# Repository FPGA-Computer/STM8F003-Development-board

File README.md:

This is a quick and dirty STM8F003 development board.

Initial PCB release - first layout/non-tested

PCB/ Eagle CAD files and Sketch3D model

Project page is at 
http://hw-by-design.blogspot.com/2018/07/stm8-breakout-board-with-usb-serial.html

This work is licensed under a 
Attribution 4.0 International (CC BY 4.0)

The full detail of this license is available at: 
https://creativecommons.org/licenses/by/4.0/

I messed up on the CC license version number on the CAD.  Treat it as 4.0.

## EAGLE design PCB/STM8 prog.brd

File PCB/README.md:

This is a quick and dirty STM8F003 development board.

Initial PCB release - first layout/non-tested

PCB/  - Eagle CAD filesand Sketch3D model

Hackaday project page is at 
https://hackaday.io/project/18286-misc-8-bit-uc-projects/log/54286-stm8-breakout-board-with-usb-serial

This work is licensed under a 
Attribution 4.0 International (CC BY 4.0)

The full detail of this license is available at: 
https://creativecommons.org/licenses/by/4.0/

I messed up on the CC license version number on the CAD.  Treat it as 4.0.

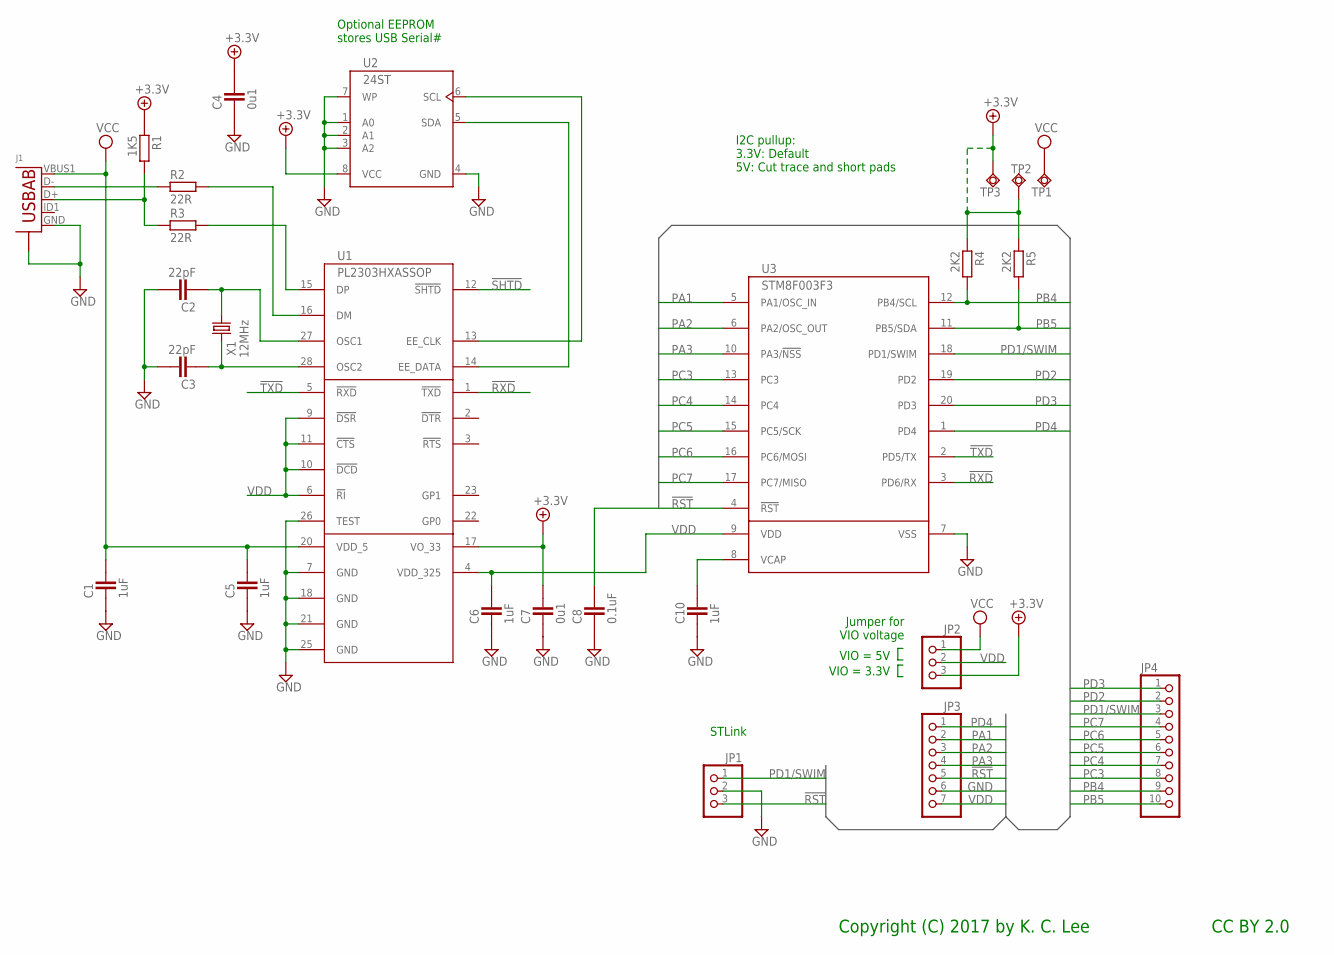
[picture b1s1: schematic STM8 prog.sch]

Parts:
C1, C5, C6, C10: 1uF; CAPC1608X92N
C2, C3: 22pF; CAPC1608X92N
C4, C7: 0u1; CAPC1608X92N
C8: 0.1uF; CAPC1608X92N
J1: USB-ABBG; USB-AB-MICRO-SMD_V03_SF
JP1, JP2: PINHD-1X3; 1X03
JP3: PINHD-1X7_2.54; 1X07
JP4: PINHD-1X10; 1X10
R1: 1K5; RESC1608X55N
R2, R3: 22R; RESC1608X55N
R4, R5: 2K2; RESC1608X55N
TP1, TP2, TP3: TPSQTP09SQ; TP09SQ
U1: PL2303HXASSOP; SSOP28DB
U2: 24ST; TSSOP8
U3: STM8F003F3; TSSOP20
X1: 12MHz; HC49U-V

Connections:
!RST: C8.2, JP1.3, JP3.5, U3.4 (!RST)
!RXD: U1.1 (!TXD), U3.3 (PD6/RX)
!SHTD: U1.12 (!SHTD)
!TXD: U1.5 (!RXD), U3.2 (PD5/TX)
+3.3V: C4.2, C7.2, JP2.3, R1.1, R4.1, R5.1, TP2.TP, TP3.TP, U1.17 (VO_33), U2.8 (VCC)
GND: C1.1, C2.2, C3.2, C4.1, C5.1, C6.1, C7.1, C8.1, C10.1, J1.GND, J1.S1 (S), J1.S2 (S), J1.S3 (S), J1.S4 (S), JP1.2, JP3.6, U1.7 (GND), U1.18 (GND), U1.21 (GND), U1.25 (GND), U1.26 (TEST), U2.1 (A0), U2.2 (A1), U2.3 (A2), U2.4 (GND), U2.7 (WP), U3.7 (VSS)
unnamed: C10.2, U3.8 (VCAP)
unnamed: R3.2, U1.15 (DP)
unnamed: J1.D+, R1.2, R3.1
unnamed: J1.D-, R2.1
unnamed: R2.2, U1.16 (DM)
unnamed: U1.14 (EE_DATA), U2.5 (SDA)
unnamed: U1.13 (EE_CLK), U2.6 (SCL)
unnamed: C2.1, U1.27 (OSC1), X1.1
unnamed: C3.1, U1.28 (OSC2), X1.2
PA1: JP3.2, U3.5 (PA1/OSC_IN)
PA2: JP3.3, U3.6 (PA2/OSC_OUT)
PA3: JP3.4, U3.10 (PA3/!NSS)
PB4: JP4.9, R4.2, U3.12 (PB4/SCL)
PB5: JP4.10, R5.2, U3.11 (PB5/SDA)
PC3: JP4.8, U3.13 (PC3)
PC4: JP4.7, U3.14 (PC4)
PC5: JP4.6, U3.15 (PC5/SCK)
PC6: JP4.5, U3.16 (PC6/MOSI)
PC7: JP4.4, U3.17 (PC7/MISO)
PD1/SWIM: JP1.1, JP4.3, U3.18 (PD1/SWIM)
PD2: JP4.2, U3.19 (PD2)
PD3: JP4.1, U3.20 (PD3)
PD4: JP3.1, U3.1 (PD4)
VCC: C1.2, C5.2, J1.VBUS1 (VBUS), JP2.1, TP1.TP, U1.20 (VDD_5)
VDD: C6.2, JP2.2, JP3.7, U1.4 (VDD_325), U1.6 (!RI), U1.9 (!DSR), U1.10 (!DCD), U1.11 (!CTS), U3.9 (VDD)

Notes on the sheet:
VIO = 5V
VIO = 3.3V
Jumper for VIO voltage
STLink
Copyright (C) 2017 by K. C. Lee
CC BY 2.0
I2C pullup: 3.3V: Default 5V: Cut trace and short pads
Optional EEPROM stores USB Serial#

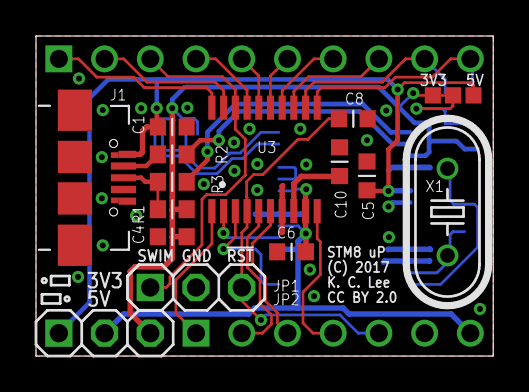
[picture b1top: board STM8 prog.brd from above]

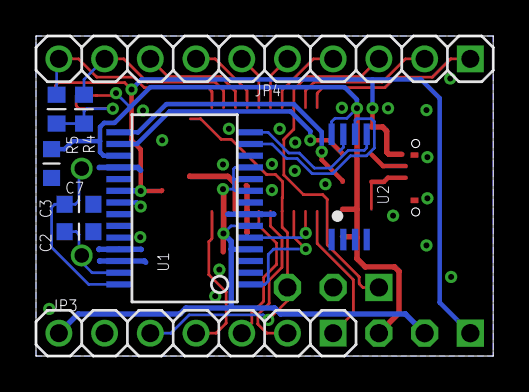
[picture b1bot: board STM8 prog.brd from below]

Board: 2 copper layers, 25.4 x 17.8 mm, 26 parts (9 on the bottom side), 30 nets.

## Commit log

2017-03-05 Board Rev 0 release
2017-03-05 typo
2017-03-05 cleanup
2018-07-30 Change of address
